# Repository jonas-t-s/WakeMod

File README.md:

# WakeMod: An Open-Source Wake-up Transceiver Module

WakeMod is an open-source, ultra-low-power wake-up transceiver module designed for the 868 MHz ISM band,
facilitating easy integration of Wake-up Radio (WuR) capabilities into existing and new IoT systems. It aims
to significantly reduce idle power consumption while ensuring low-latency event responsiveness, crucial for
battery-powered, long-term deployments.

An in-depth analysis of the hardware can be found here: [arXiv](https://arxiv.org/abs/2505.21529)

> <div align="justify"> Large-scale IoT applications, such as asset tracking and remote sensing, demand multi-year battery lifetimes to minimize maintenance and operational costs. Traditional wireless protocols often employ duty cycling, introducing a tradeoff between latency and idle consumption -- both unsuitable for event-driven and ultra-low power systems. A promising approach to address these issues is the integration of always-on Wake-up Receivers (WuRs). They provide asynchronous, ultra-low power communication to overcome these constraints. This paper presents WakeMod, an open-source wake-up transceiver module for the 868 MHz ISM band. Designed for easy integration and ultra-low power consumption, it leverages the -75 dBm sensitive FH101RF WuR. WakeMod achieves a low idle power consumption of 6.9 µW while maintaining responsiveness with a sensitivity of -72.6 dBm. Reception of a wake-up call is possible from up to 130 m of distance with a -2.1 dBi antenna, consuming 17.7 µJ with a latency below 54.3 ms. WakeMod's capabilities have further been demonstrated in an e-ink price tag application, achieving 7.17 µW idle consumption and enabling an estimated 8-year battery life with daily updates on a standard CR2032 coin cell. WakeMod offers a practical solution for energy-constrained, long-term IoT deployments, requiring low-latency, and on-demand communication.</div>

If you use *WakeMod* in an academic or industrial context, please cite the following publication:

```bibtex
@misc{schultess25_wakem,
  author         = {Lukas Schulthess and Silvano Cortesi and Michele Magno},
  title          = {Wakemod: a 6.9uw Wake-Up Radio Module With -72.6dbm Sensitivity for On-Demand Iot},
  year           = 2025,
  doi            = {10.48550/ARXIV.2505.21529},
  url            = {https://arxiv.org/abs/2505.21529},
  eprint         = {2505.21529},
  archiveprefix  = {arXiv},
  primaryclass   = {cs.NI},
  DATE_ADDED     = {Sun Jun 1 12:42:45 2025},
}
```

## Features

*   Combines Wake-up Radio (WuR) Receiver and OOK Transmitter functionality.
*   Ultra-low power operation:
    *   Module idle consumption: 6.9 µW
    *   WuR sensitivity: -72.6 dBm
*   Onboard low-power STMicroelectronics STM32U031 MCU for control and I2C communication.
*   Frauenhofer FH101RF Wake-up Radio receiver (868.35 MHz).
*   Maxim Integrated MAX41462 OOK transmitter (868.35 MHz).
*   Analog Devices ADG918 RF switch for single antenna operation.
*   Standard I2C interface for communication with a host system.
*   Compact RFM69x-compatible footprint (16mm x 16mm).
*   Deep sleep mode controlled by `SYS_SDN` pin.
*   Interrupt output (`SYS_IRQ`) to signal received Wake-up Calls to the host.
*   Supports 6-byte custom payload transmission and reception.

## Hardware

*   **Main Components:**
    *   MCU: STMicroelectronics STM32U031
    *   WuR Receiver: Fraunhofer IIS FH101RF
    *   OOK Transmitter: Analog Devices MAX41462
    *   RF Switch: Analog Devices ADG918
*   **Footprint:** RFM69HW compatible (16mm x 16mm)
*   **Operating Frequency:** 868.35 MHz

### Pinout

| Pin Name  | Type   | Description                                                                    |
| :-------- | :----- | :----------------------------------------------------------------------------- |
| `VDD`     | Power  | Power Supply Voltage                                                           |
| `GND`     | Ground | Ground Connection                                                              |
| `SDA`     | I/O    | I2C Data Line                                                                  |
| `SCL`     | Input  | I2C Clock Line                                                                 |
| `SYS_SDN` | Input  | System Shutdown / Module Enable. **Active Low.** High for deep sleep.          |
| `SYS_IRQ` | Output | Interrupt Request to Host. **Active High.** Signals a Wake-up event occurred.  |
| `ANT`     | RF     | Antenna connection                                                             |

**Note:** While the footprint matches RFM69, the interface is **I2C**, not SPI. All other pins are currently unused.

## Firmware

The firmware architecture of the WakeMod module is optimized for ultra-low power consumption, keeping the
STM32U031 MCU in shutdown mode as much as possible. Critical data is retained in backup registers during
shutdown.

The MCU wakes up based on three primary sources:
1.  **System Reset:** The MCU transitions immediately back to shutdown to minimize power consumption.
2.  **WuR IRQ:** Upon a wake-up triggered by the FH101RF (e.g., address match), the module clears the
interrupt, retrieves the interrupt source and up to 6 bytes of payload data from the WuR. This information is
stored in the MCU's backup registers. The host MCU's `SYS_IRQ` pin is then asserted, and the module returns to     shutdown.
3.  **SYS_SDN Pin:** If the `SYS_SDN` pin transitions to low, the MCU wakes up and prepares its I2C slave     interface to receive commands from the host. When `SYS_SDN` returns high, the module re-enters shutdown.

## WakeMod as a Module: Detailed Usage

### Power States

*   **Active Mode:** When `SYS_SDN` is held LOW. The module is operational and ready to accept I2C 
commands.
*   **Deep Sleep Mode:** When `SYS_SDN` is HIGH. The module enters its lowest power state (STM32U031 in 
shutdown, peripherals off). I2C communication is disabled. The FH101RF Wake-up Radio remains functional and 
listening. To wake the module for I2C communication, bring `SYS_SDN` LOW. Allow a short time for the module to     initialize before sending I2C commands.

### Interrupt Handling (`SYS_IRQ`)

*   The `SYS_IRQ` pin becomes active (HIGH) when the FH101RF detects a valid Wake-up condition (e.g., matching address, pattern received) and the internal STM32U031 has processed this event.
*   The host system should detect this interrupt (e.g., on a rising edge).
*   After detecting the interrupt, the host should query the module using the `IRQ Reason` command (0x03) via I2C to determine the cause and retrieve any associated data.
*   Reading the `IRQ Reason` register de-asserts the `SYS_IRQ` pin. Reading it multiple times will return the same last IRQ reason until a new WuR event occurs.

### Communication Protocol (I2C)

*   **Interface:** I2C Slave
*   **Slave Address:** `0x2E` (7-bit address)
*   **Speed:** Max 10 kHz
*   **Control:** I2C communication is only possible when the `SYS_SDN` pin is LOW.

#### I2C Commands Overview

The WakeMod module supports four main commands initiated by the host MCU:

1.  **`WhoAmI` (0x00):** Reads a static device identifier. Used to verify communication.
2.  **`SetupWuR` (0x01):** Configures the FH101RF Wake-up Radio. This includes setting the 16-bit wake-up address, data rates (low and fast), and IRQ source mask. This command triggers a full calibration of the FH101RF.
3.  **`SendWuC` (0x02):** Transmits a Wake-up Call (WuC) using the MAX41462 OOK transmitter. This includes the target 16-bit wake-up address, data rates, and an optional 6-byte data payload. The internal STM32U031 
uses SPI for accurate timing of the preamble and address/payload transmission to the MAX41462.
4.  **`IRQReason` (0x03):** Retrieves the reason for the last wake-up event (from the FH101RF) and any received payload data. This data is read from the STM32U031's backup registers.

#### I2C Transaction Structure

*   **Write Operations (Host to WakeMod):**
    *   Used for `SetupWuR` (0x01) and `SendWuC` (0x02).
    *   The host initiates an I2C WRITE transaction to the slave address (`0x2E`).
    *   The host sends a total of **12 bytes** in a single transaction:
        1.  The 1-byte Command (e.g., `0x01` for `SetupWuR`).
        2.  Followed by 11 data bytes (Bytes 0-10 as defined in the table below).
    *   Example (`SendWuC`):
        `START | (0x2E << 1) | W | ACK | <CMD_BYTE (0x02)> | ACK | <Data Byte 0> | ACK | ... | <Data Byte     10> | ACK | STOP`

*   **Read Operations (Host from WakeMod):**
    *   Used for `WhoAmI` (0x00) and `IRQ Reason` (0x03).
    *   A combined I2C write-then-read sequence is used:
        1.  **Write Address Phase:** Host initiates an I2C WRITE transaction to `0x2E`. Send only **1 
byte**: the Command Byte (e.g., `0x00` for `WhoAmI`).
        2.  **Read Data Phase:** Host initiates an I2C READ transaction to `0x2E`. Read exactly **8 
bytes** of data from the module (Bytes 0-7 as defined in the table below).
    *   Example (`WhoAmI`):
        *   `START | (0x2E << 1) | W | ACK | <CMD_BYTE (0x00)> | ACK | REP_START | (0x2E << 1) | R | ACK |     <Read Byte 0> | ACK | ... | <Read Byte 7> | NACK | STOP`

#### I2C Command Byte Layout

| Command / Register       | Value | Type  | Byte 0                     | Byte 1                     | Byte 2                | Byte 3                | Byte 4                    | Byte 5                      | Byte     6             | Byte 7             | Byte 8             | Byte 9             | Byte 10            |
| :----------------------- | :---- | :---- | :------------------------- | :------------------------- | :-------------------- | :-------------------- | :------------------------ | :-------------------------- | :----------------- | :----------------- | :----------------- | :----------------- | :----------------- |
| **WhoAmI**               | 0x00  | Read  | `0x42` (ID MSB)            | `0x42` (ID LSB)            | `0x00` (Padding)      | `0x00` (Padding)      | `0x00` (Padding)          | `0x00` (Padding)            | `0x00` (Padding)   | `0x00` (Padding)   | *N/A*              | *N/A*              | *N/A*              |
| **SetupWuR**             | 0x01  | Write | Wake-up Addr [15:8]        | Wake-up Addr [7:0]         | Low     Data Rate (enum)  | Fast Data Rate (enum) | IRQ Source Mask           | (Active Branches<<2)|IDM_CTRL             | Reserved `0x00`    | Reserved `0x00`    | Reserved `0x00`    | Reserved `0x00`    | Reserved `0x00`    |
| **SendWuC**              | 0x02  | Write | Wake-up Addr [15:8]        | Wake-up Addr [7:0]         | Low     Data Rate (enum)  | Fast Data Rate (enum) | Send Add. Data Flag (LSb)   | Add. Data [0]               | Add.     Data [1]      | Add. Data [2]      | Add. Data [3]      | Add. Data [4]      | Add. Data [5]      |
| **IRQ Reason**           | 0x03  | Read  | IRQ Source Flags           | Recv Add. Data Flag (LSb)  | Received Data [0]     | Received Data [1]     | Received Data [2]         | Received Data [3]           | Received Data [4]  | Received Data [5]  | *N/A*              | *N/A*              | *N/A*              |

**Table Key:**

*   **Value:** The byte sent by the host to select the command/register.
*   **Type:** Indicates if the operation is a Read from or Write to the module *from the host's 
perspective*.
*   **Bytes 0-10 (Write):** Data payload sent by the host *after* the Command Byte for write operations. 
Total 11 data bytes.
*   **Bytes 0-7 (Read):** Data payload returned by the module during the read phase of a read operation. 
Total 8 data bytes.
*   **Wake-up Addr [15:8]:** Most Significant Byte (MSB) of the 16-bit Wake-up Address.
*   **Wake-up Addr [7:0]:** Least Significant Byte (LSB) of the 16-bit Wake-up Address.
*   **Data Rate (enum):** See `phy_speed` Enum Values table below.
*   **IRQ Source Mask/Flags:** See IRQ Source Bits table below. Bitmask used in `SetupWuR` (Byte 4) to 
enable specific FH101RF interrupt sources, or flags indicating occurred interrupts in `IRQ Reason` (Byte 0).
*   **Send Add. Data Flag (LSb):** Least Significant Bit of Byte 4 for `SendWuC`. `1` = Additional Data in     Bytes 5-10 (Add. Data [0-5]) is valid and should be sent. `0` = Additional Data is ignored (but bytes 5-10 
must still be sent, typically as `0x00`).
*   **Recv Add. Data Flag (LSb):** Least Significant Bit of Byte 1 for `IRQ Reason`. `1` = Received Data 
in Bytes 2-7 (Received Data [0-5]) is valid. `0` = No valid received data (Bytes 2-7 may be undefined).
*   **Add. Data [0-5] / Received Data [0-5]:** The 6-byte additional data payload for transmission or 
reception.
*   **Reserved / Padding:** These bytes must be included in the I2C transaction but their value is 
typically ignored or should be `0x00`. They ensure the fixed transaction length.
*   ***N/A*:** Not applicable for that transaction type (Reads return 8 data bytes, Writes expect 11 data     bytes following the command byte).

#### Data Definitions

##### `phy_speed` Enum Values (as per `OLDREADME.md` I2C values)
These values are used in the `SetupWuR` and `SendWuC` commands for the Low/Fast Data Rate bytes.

| Value (for I2C) | Speed (bps) |
| :-------------- | :---------- |
| 0x02            | 1024        |
| 0x03            | 2048        |
| 0x04            | 4096        |
| 0x05            | 8192        |
| 0x06            | 16384       |
| 0x07            | 32768       |

*Note:* For OOK transmission via MAX41462, data rates below 1024 bps (e.g., 256, 512 bps) do not work due to the MAX41462's auto-shutdown functionality. The FH101RF itself supports these lower rates for reception.

##### IRQ Source Bits (Byte 4 in `SetupWuR` / Byte 0 in `IRQ Reason`)
This byte indicates the cause of the interrupt (`IRQ Reason`) or configures which FH101RF events can cause an interrupt (`SetupWuR`). Multiple bits can be set. These bits correspond to the FH101RF's interrupt 
sources.

| Bit | Description                  | Notes (Primarily for FH101RF internal events)             |
| :-- | :--------------------------- | :-------------------------------------------------------- |
| 7   | Cyclic Timer Alarm           | Cyclic timer target reached.                              |
| 6   | RTC Timer Alarm              | One of the 4 RTC timers reached its target.               |
| 5   | ID Match & LDR               | Valid ID received, followed by transition to LDR mode.    |
| 4   | ID Match & FIFO Filled       | Valid ID received, followed by FIFO being filled.         |
| 3   | Correlation Pattern Match    | OOK data matches selected correlation sequence.           |
| 2   | FIFO Buffer Filled           | FIFO filled to configured length (e.g. 6 bytes for payload).|
| 1   | FIFO Overflow                | More data received than FIFO capacity.                    |
| 0   | ID Match                     | Received Fast Data Packet matches configured 16-bit ID.   |

### Basic Usage Flow

1.  **Power On & Enable:** Ensure `VDD` and `GND` are connected. Pull `SYS_SDN` LOW to enable the module. Wait briefly for startup if it was in deep sleep.
2.  **(Optional) Verify Communication:** Perform a `WhoAmI` (0x00) read sequence. Check for `0x4242` in 
the first two bytes.
3.  **Configure Receiver:** Perform a `SetupWuR` (0x01) write sequence with:
    *   Your desired 16-bit `Wake-up Address`.
    *   The `Low Data Rate` and `Fast Data Rate` (see `phy_speed` enum).
    *   The `IRQ Source Mask` to enable interrupts for relevant events (e.g., bit 0 for ID Match, bit 4 
for ID Match & FIFO Filled if expecting payload).
4.  **Enter Low Power (Host):** The host can now enter its own low-power mode, monitoring the `SYS_IRQ` 
pin. The WakeMod is now listening. Make sure `SYS_SDN` is pulled high for WakeMod to enter low-power state.
5.  **Handle Interrupt from WakeMod:** When `SYS_IRQ` goes HIGH:
    *   The host wakes up.
    *   Perform an `IRQ Reason` (0x03) read sequence (possibly short delay needed before readout).
    *   Parse `Byte 0` (IRQ Source Flags) to understand why the interrupt occurred.
    *   Check `Byte 1` (Recv Add. Data Flag). If its LSB is `1`, the 6 bytes of `Received Data` (Bytes 
2-7) are valid. Process this data.
    *   The read operation of `IRQ Reason` clears the `SYS_IRQ` pin on the WakeMod.
6.  **(Optional) Transmit a Wake-up Call:** If the host needs to wake another device:
    *   Ensure `SYS_SDN` is LOW.
    *   Perform a `SendWuC` (0x02) write sequence with:
        *   The target device's 16-bit `Wake-up Address`.
        *   `Low Data Rate` and `Fast Data Rate`.
        *   `Send Add. Data Flag` (set LSB of Byte 4 to `1` if sending payload).
        *   The 6-byte `Add. Data` payload (Bytes 5-10) if applicable.
7.  **Enter Deep Sleep (WakeMod):** When I2C communication is not needed for extended periods, set 
`SYS_SDN` HIGH to put the WakeMod into its lowest power deep sleep mode. The WuR (FH101RF) remains active.

## Folder Structure

*   `fw/Core/Src`: Contains the main source files for the STM32U031 firmware, including `main.c`, `i2c_slave.c` (I2C command handling), `utils.c` (helper functions), and HAL drivers.
*   `fw/Core/Inc`: Contains the corresponding header files, including `main.h`, `utils.h` (definitions, enums).
*   Other folders (`Drivers`, `Middlewares`, etc.) contain STM32CubeMX generated files and libraries.

## License

See the `LICENSE` file of the firmware respective hardware for details.

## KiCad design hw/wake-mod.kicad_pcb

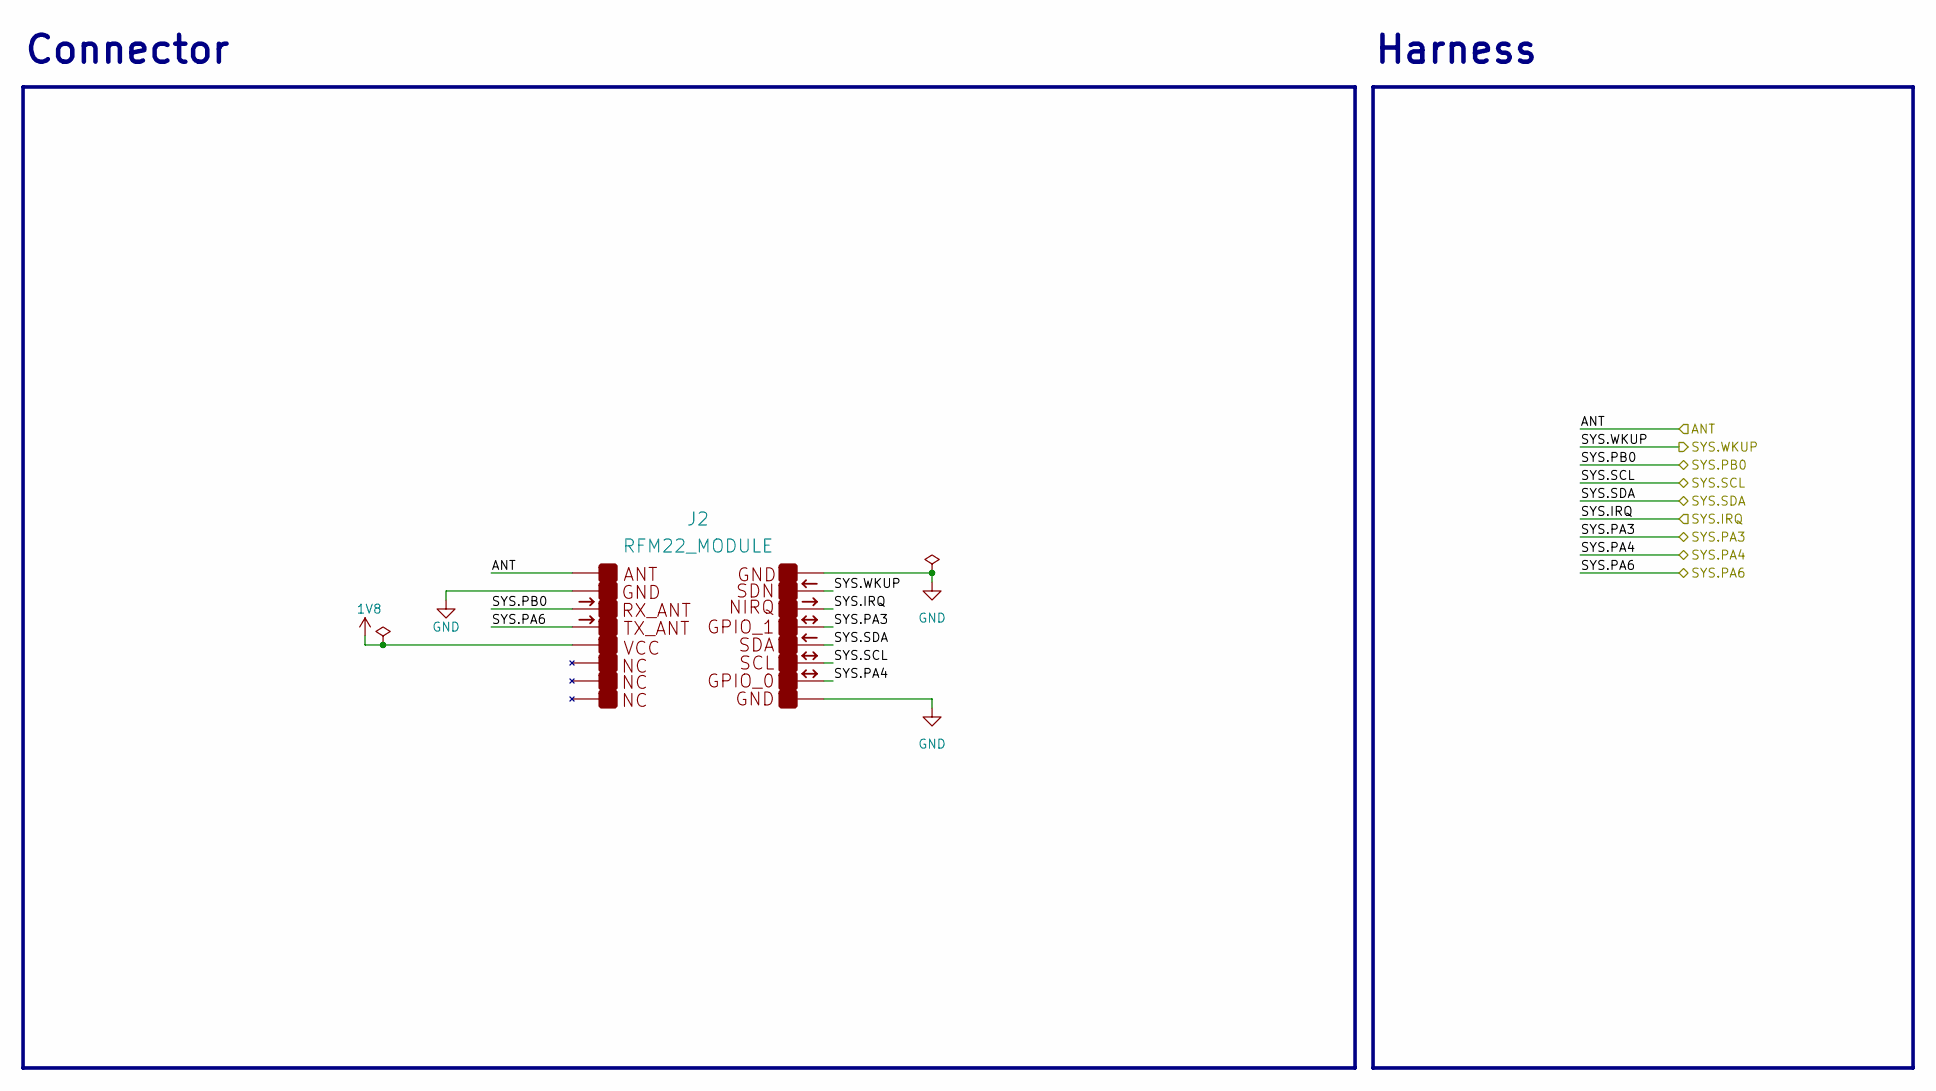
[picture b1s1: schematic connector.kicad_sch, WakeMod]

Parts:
J2: RFM22_MODULE; MPN RFM22_MODULE

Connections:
1V8: J2.5 (VCC); also elsewhere on the board
/connector/ANT: J2.1 (ANT); also elsewhere on the board
/connector/SYS.IRQ: J2.14 (NIRQ); also elsewhere on the board
/connector/SYS.PA3: J2.13 (GPIO_4); also elsewhere on the board
/connector/SYS.PA4: J2.10 (GPIO_3); also elsewhere on the board
/connector/SYS.PA6: J2.4 (TX_ANT); also elsewhere on the board
/connector/SYS.PB0: J2.3 (RX_ANT); also elsewhere on the board
/connector/SYS.SCL: J2.11 (SCL); also elsewhere on the board
/connector/SYS.SDA: J2.12 (SDA); also elsewhere on the board
/connector/SYS.WKUP: J2.15 (SDN); also elsewhere on the board
GND: J2.2 (GND), J2.9 (GND), J2.16 (GND); also elsewhere on the board

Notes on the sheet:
Harness
Connector

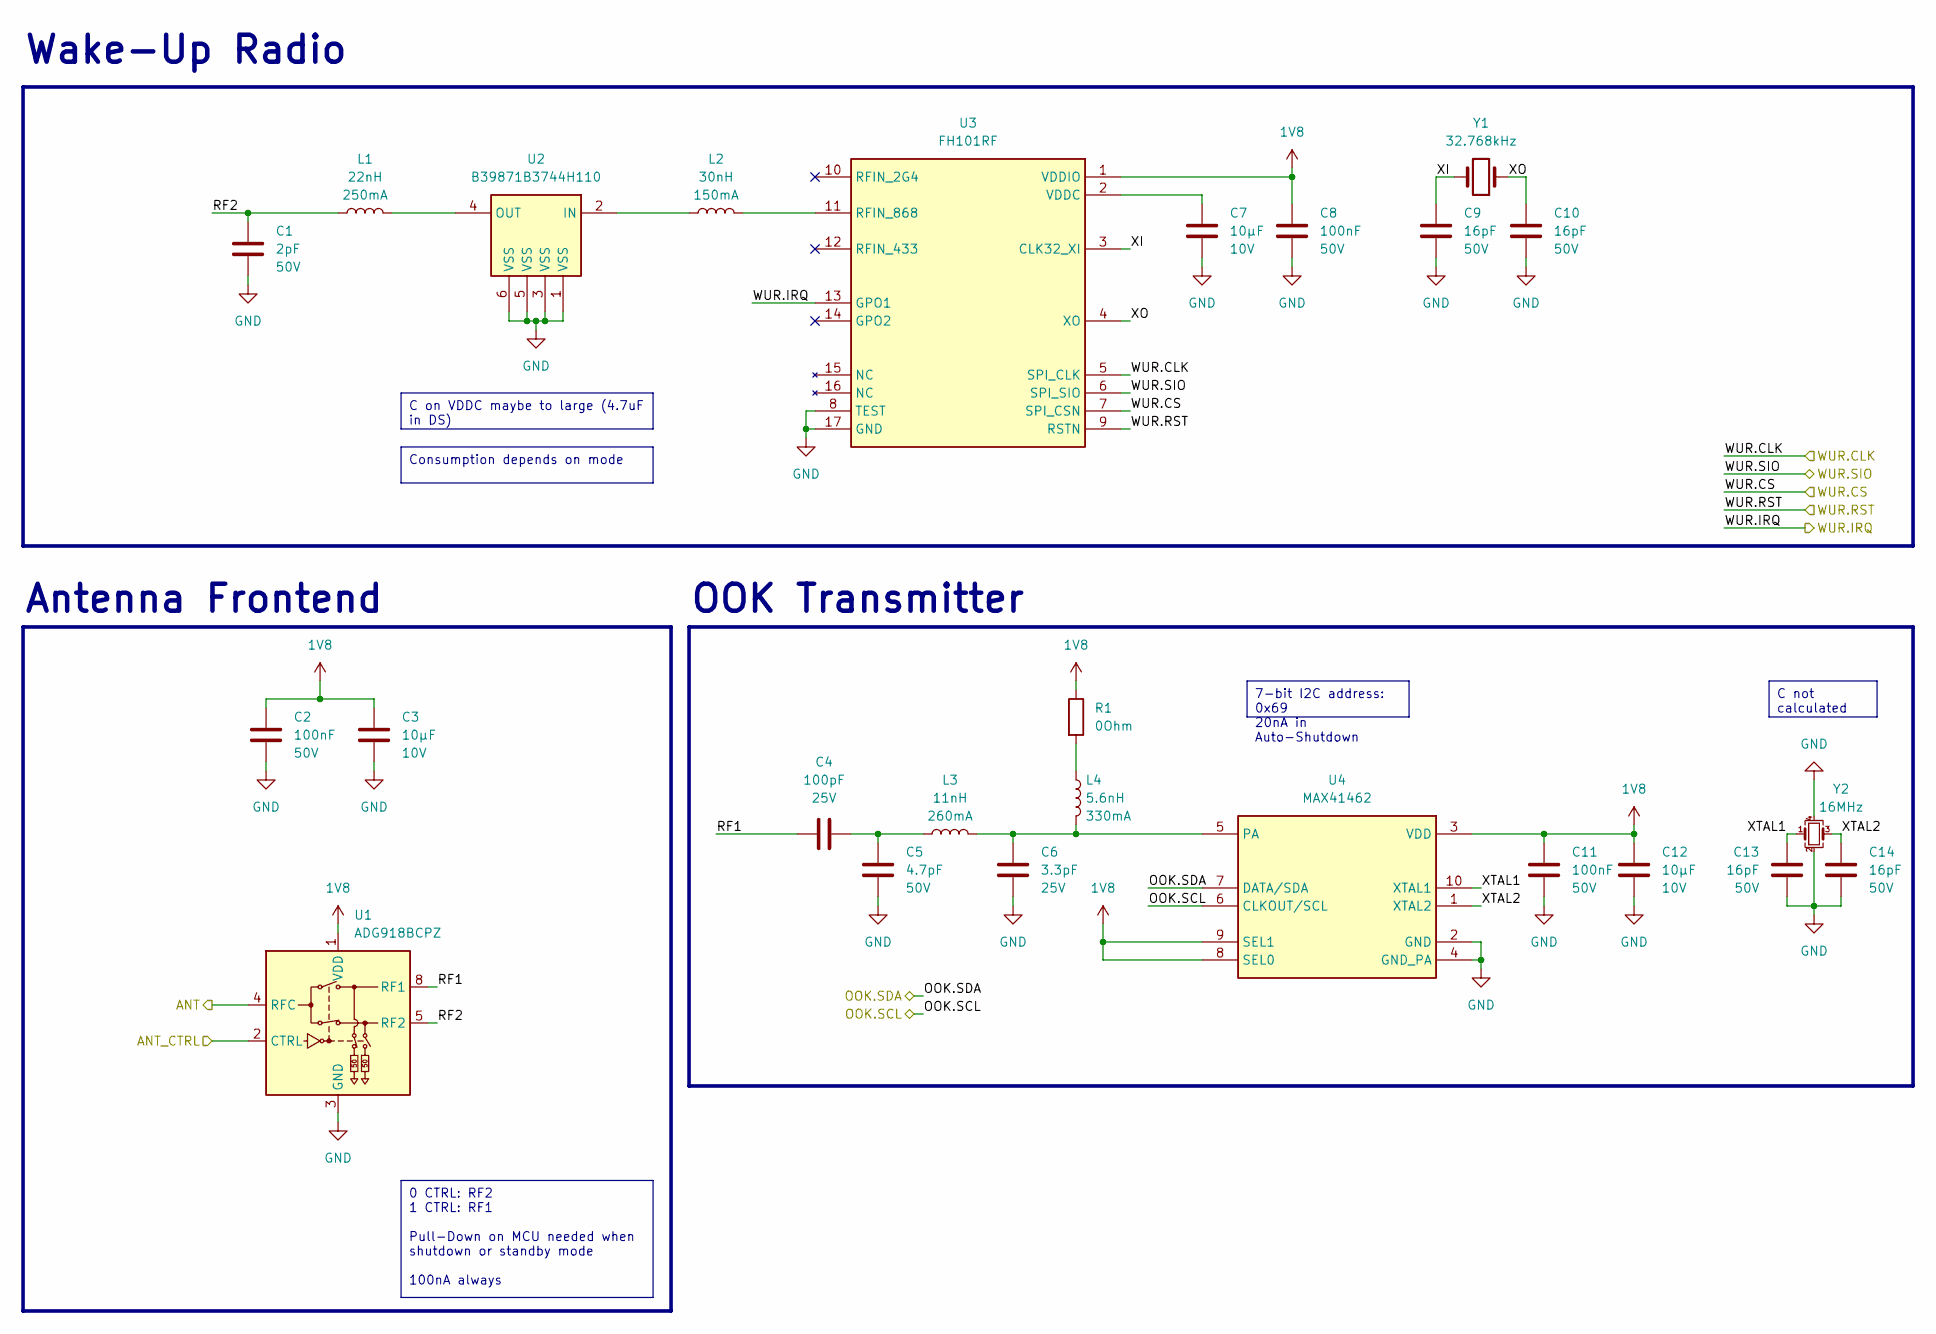
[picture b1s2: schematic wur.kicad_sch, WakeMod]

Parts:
C1: 2pF; C_0201_0603Metric; Voltage 50V; Tolerance 0.05pF; MPN GJM0335C1H2R0WB01D
C2, C8, C11: 100nF; C_0402_1005Metric; Voltage 50V; Tolerance 10%; MPN GRM155R71H104KE14J
C3, C7, C12: 10μF; C_0402_1005Metric; Voltage 10V; Tolerance 20%; MPN GRM155R61A106ME11D
C4: 100pF; C_0201_0603Metric; Voltage 25V; Tolerance 1%; MPN GRM0335C1E101FA01D
C5: 4.7pF; C_0201_0603Metric; Voltage 50V; Tolerance 0.05pF; MPN GJM0335C1H4R7WB01D
C6: 3.3pF; C_0201_0603Metric; Voltage 25V; Tolerance 0.05pF; MPN GJM0335C1E3R3WB01D
C9, C10, C13, C14: 16pF; C_0402_1005Metric; Voltage 50V; Tolerance 5%; MPN GRM1555C1H160JA01D
L1: 22nH; L_0201_0603Metric; Tolerance 3%; MPN LQP03HQ22NH02D
L2: 30nH; L_0201_0603Metric; Tolerance 3%; MPN LQP03HQ30NH02D
L3: 11nH; L_0201_0603Metric; Tolerance 5%; MPN LQW03AW11NJ00D
L4: 5.6nH; L_0201_0603Metric; Tolerance 5%; MPN LQW03AW5N6J00D
R1: 0Ohm; R_0201_0603Metric; Tolerance 1.00%; MPN ERJ-1GN0R00C
U1: ADG918BCPZ; LFCSP-8-1EP_3x3mm_P0.5mm_EP1.45x1.74mm; MPN ADG918BCPZ
U2: B39871B3744H110; QUALCOMM_B3744; MPN B39871B3744H110
U3: FH101RF; RFICIENT_QFN-16; MPN FH101RF
U4: MAX41462; MAXIM_MINI-SO-10; MPN MAX41462
Y1: 32.768kHz; ECS_ECX-12R; MPN ECS-.327-12.5-12R
Y2: 16MHz; Oscillator_SMD_SeikoEpson_SG210-4Pin_2.5x2.0mm; MPN ECS-160-8-36-CKM

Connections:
1V8: C2.2, C3.1, C8.1, C11.1, C12.1, R1.1, U1.1 (VDD), U3.1 (VDDIO), U4.3 (VDD), U4.8 (SEL0), U4.9 (SEL1); also elsewhere on the board
/connector/ANT: U1.4 (RFC); also elsewhere on the board
/mcu/ANT_CTRL: U1.2 (CTRL); also elsewhere on the board
/mcu/OOK.SCL: U4.6 (CLKOUT/SCL); also elsewhere on the board
/mcu/OOK.SDA: U4.7 (DATA/SDA); also elsewhere on the board
/mcu/WUR.CLK: U3.5 (SPI_CLK); also elsewhere on the board
/mcu/WUR.CS: U3.7 (SPI_CSN); also elsewhere on the board
/mcu/WUR.IRQ: U3.13 (GPO1); also elsewhere on the board
/mcu/WUR.RST: U3.9 (RSTN); also elsewhere on the board
/mcu/WUR.SIO: U3.6 (SPI_SIO); also elsewhere on the board
/wur/RF1: C4.1, U1.8 (RF1)
/wur/RF2: C1.1, L1.1, U1.5 (RF2)
/wur/XI: C9.1, U3.3 (CLK32_XI), Y1.1
/wur/XO: C10.1, U3.4 (XO), Y1.2
/wur/XTAL1: C13.1, U4.10 (XTAL1), Y2.1
/wur/XTAL2: C14.1, U4.1 (XTAL2), Y2.3
GND: C1.2, C2.1, C3.2, C5.2, C6.2, C7.2, C8.2, C9.2, C10.2, C11.2, C12.2, C13.2, C14.2, U1.3 (GND), U1.6 (GND), U1.7 (GND), U1.9 (GND), U2.1 (VSS), U2.3 (VSS), U2.5 (VSS), U2.6 (VSS), U3.8 (TEST), U3.17 (GND), U4.2 (GND), U4.4 (GND_PA), Y2.2, Y2.4; also elsewhere on the board
unnamed: C4.2, C5.1, L3.1
unnamed: L4.1, R1.2
unnamed: L2.1, U2.2 (IN)
unnamed: L1.2, U2.4 (OUT)
unnamed: L2.2, U3.11 (RFIN_868)
unnamed: C7.1, U3.2 (VDDC)
unnamed: C6.1, L3.2, L4.2, U4.5 (PA)

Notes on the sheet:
Wake-Up Radio
OOK Transmitter
Antenna Frontend
C on VDDC maybe to large (4.7uF in DS)
Consumption depends on mode
7-bit I2C address: 0x69 20nA in Auto-Shutdown
0 CTRL: RF2 1 CTRL: RF1 Pull-Down on MCU needed when shutdown or standby mode 100nA always
C not calculated

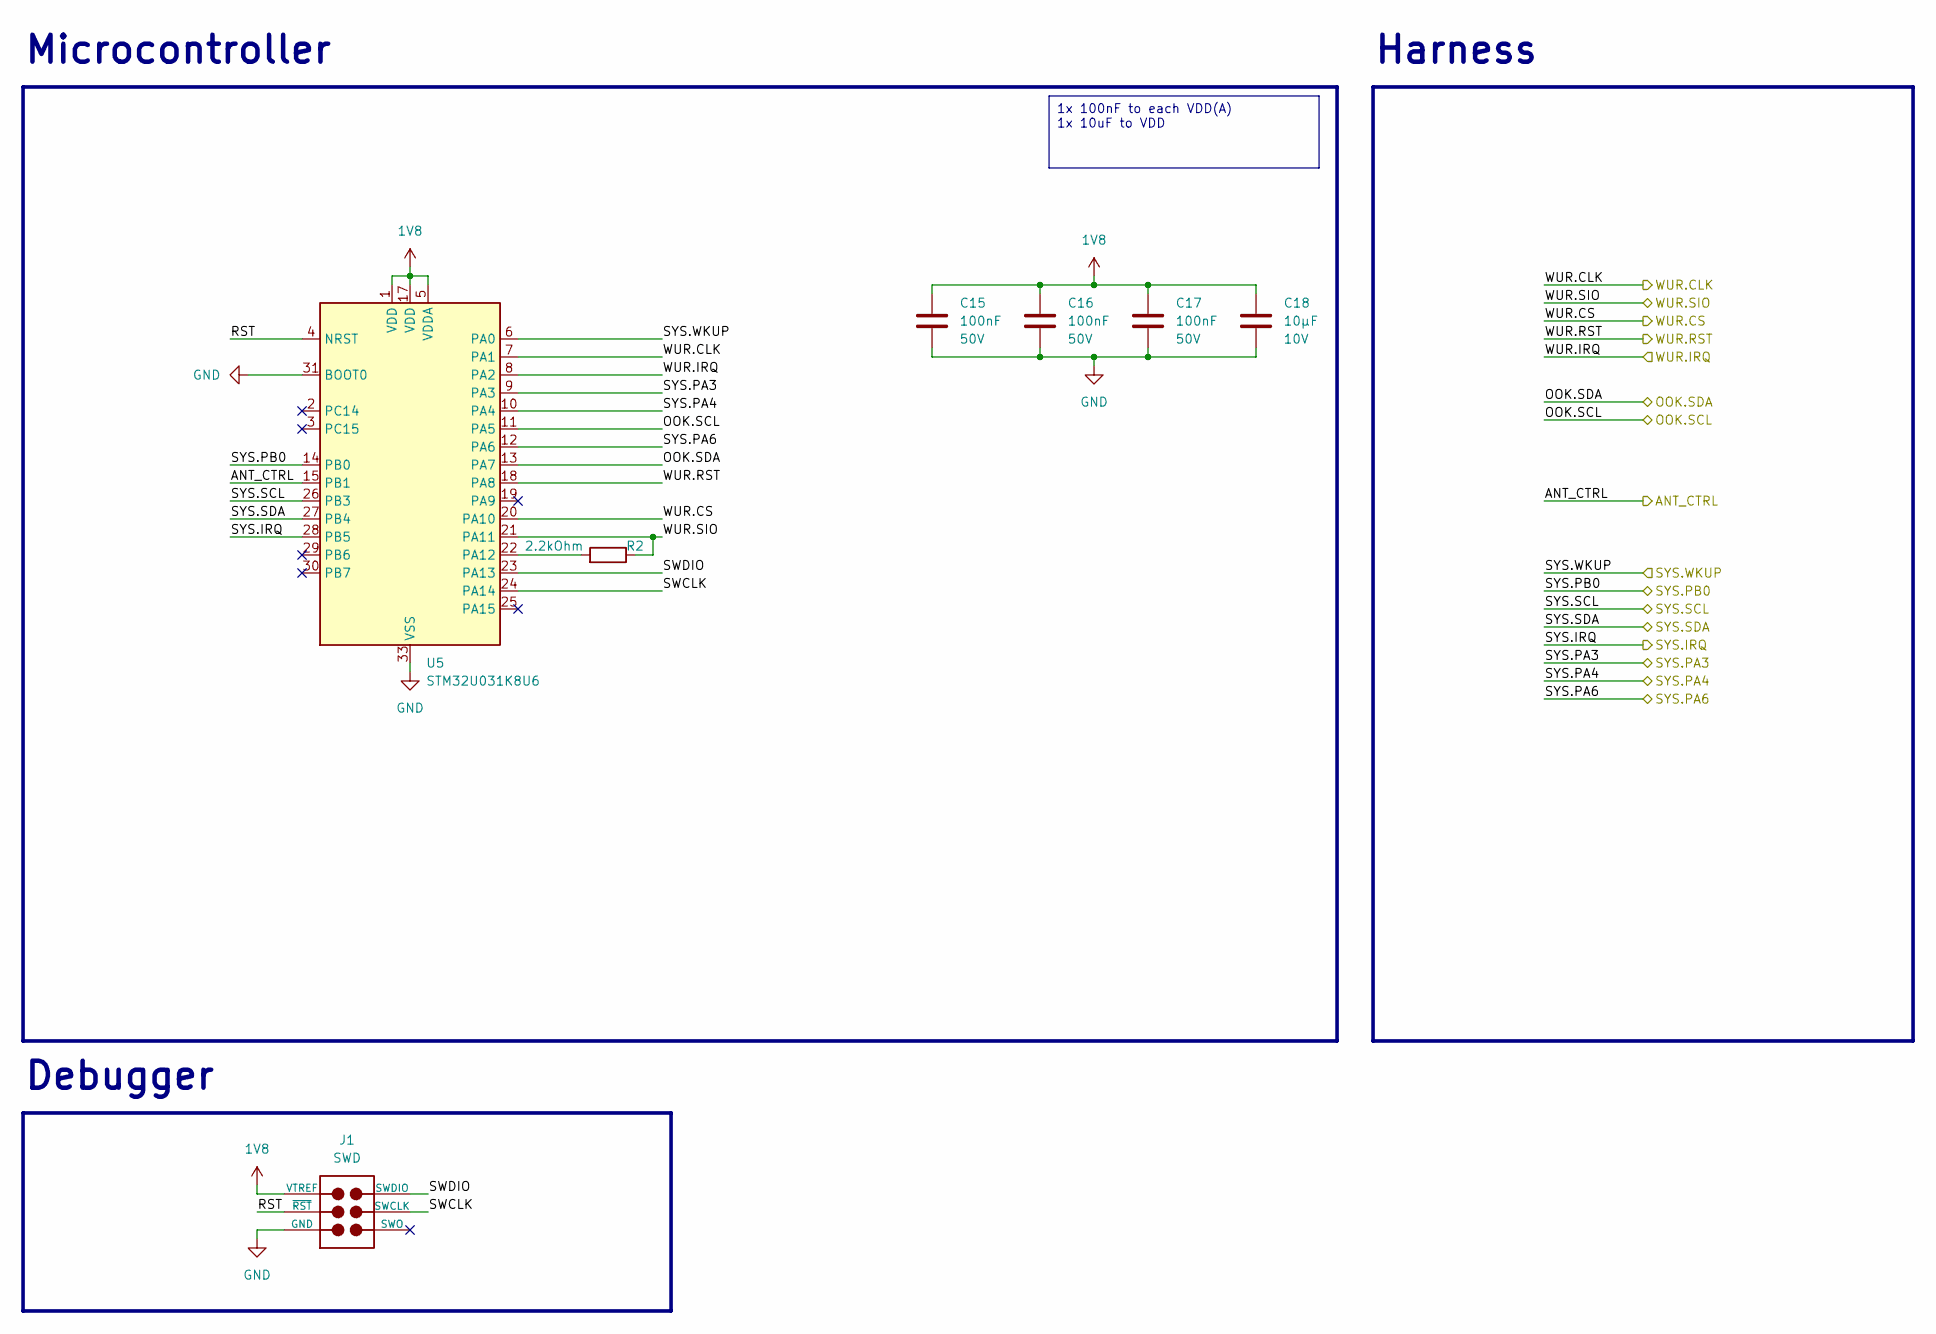
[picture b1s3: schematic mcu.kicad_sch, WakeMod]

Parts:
C15, C16, C17: 100nF; C_0402_1005Metric; Voltage 50V; Tolerance 10%; MPN GRM155R71H104KE14J
C18: 10μF; C_0402_1005Metric; Voltage 10V; Tolerance 20%; MPN GRM155R61A106ME11D
J1: SWD; TAGCONNECT_TC2030-MCP-NL
R2: 2.2kOhm; R_0402_1005Metric; Tolerance 1.00%; MPN ERJ-2RKF2201X
U5: STM32U031K8U6; QFN-32-1EP_5x5mm_P0.5mm_EP3.45x3.45mm; MPN STM32U031K8U6

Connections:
1V8: C15.1, C16.1, C17.1, C18.1, J1.1 (VTREF), U5.1 (VDD), U5.5 (VDDA), U5.17 (VDD); also elsewhere on the board
/connector/SYS.IRQ: U5.28 (PB5); also elsewhere on the board
/connector/SYS.PA3: U5.9 (PA3); also elsewhere on the board
/connector/SYS.PA4: U5.10 (PA4); also elsewhere on the board
/connector/SYS.PA6: U5.12 (PA6); also elsewhere on the board
/connector/SYS.PB0: U5.14 (PB0); also elsewhere on the board
/connector/SYS.SCL: U5.26 (PB3); also elsewhere on the board
/connector/SYS.SDA: U5.27 (PB4); also elsewhere on the board
/connector/SYS.WKUP: U5.6 (PA0); also elsewhere on the board
/mcu/ANT_CTRL: U5.15 (PB1); also elsewhere on the board
/mcu/OOK.SCL: U5.11 (PA5); also elsewhere on the board
/mcu/OOK.SDA: U5.13 (PA7); also elsewhere on the board
/mcu/RST: J1.3 (~RST), U5.4 (NRST)
/mcu/SWCLK: J1.4 (SWCLK), U5.24 (PA14)
/mcu/SWDIO: J1.2 (SWDIO), U5.23 (PA13)
/mcu/WUR.CLK: U5.7 (PA1); also elsewhere on the board
/mcu/WUR.CS: U5.20 (PA10); also elsewhere on the board
/mcu/WUR.IRQ: U5.8 (PA2); also elsewhere on the board
/mcu/WUR.RST: U5.18 (PA8); also elsewhere on the board
/mcu/WUR.SIO: R2.1, U5.21 (PA11); also elsewhere on the board
GND: C15.2, C16.2, C17.2, C18.2, J1.5 (GND), U5.16 (VSS), U5.31 (BOOT0), U5.32 (VSS), U5.33 (VSS); also elsewhere on the board
unnamed: R2.2, U5.22 (PA12)

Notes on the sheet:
Debugger
Harness
Microcontroller
1x 100nF to each VDD(A) 1x 10uF to VDD

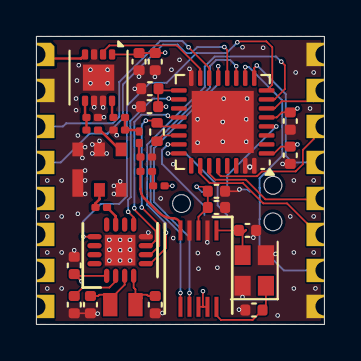
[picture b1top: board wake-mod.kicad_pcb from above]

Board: 4 copper layers, 16.0 x 16.0 mm, 33 parts (1 on the bottom side), 36 nets.

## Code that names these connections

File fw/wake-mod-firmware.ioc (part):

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Mcu.Name=STM32U031K8Ux
Mcu.Package=UFQFPN32
Mcu.UserName=STM32U031K8Ux
PA0-CK_IN.GPIOParameters=GPIO_Label
PA0-CK_IN.GPIO_Label=SYS_SDN
PA0-CK_IN.Signal=GPXTI0
PA1.GPIOParameters=GPIO_Label
PA1.GPIO_Label=WUR_CLK
PA1.Mode=Full_Duplex_Master
PA1.Signal=SPI2_SCK
PA10.GPIOParameters=PinState,GPIO_PuPd,GPIO_Label
PA10.GPIO_Label=WUR_CS
PA10.GPIO_PuPd=GPIO_PULLUP
PA10.PinState=GPIO_PIN_SET
PA10.Signal=GPIO_Output
PA11\ [PA9].GPIOParameters=GPIO_Label
PA11\ [PA9].GPIO_Label=WUR_MISO
PA11\ [PA9].Mode=Full_Duplex_Master
PA11\ [PA9].Signal=SPI2_MISO
PA12\ [PA10].GPIOParameters=GPIO_Label
PA12\ [PA10].GPIO_Label=WUR_MOSI
PA12\ [PA10].Mode=Full_Duplex_Master
PA12\ [PA10].Signal=SPI2_MOSI
PA13\ (SWDIO).GPIOParameters=GPIO_Label
PA13\ (SWDIO).GPIO_Label=SWDIO
PA13\ (SWDIO).Mode=Serial_Wire
PA13\ (SWDIO).Signal=DEBUG_JTMS-SWDIO
PA14\ (SWCLK).GPIOParameters=GPIO_Label
PA14\ (SWCLK).GPIO_Label=SWCLK
PA14\ (SWCLK).Mode=Serial_Wire
PA14\ (SWCLK).Signal=DEBUG_JTCK-SWCLK
PA2.GPIOParameters=GPIO_Label
PA2.GPIO_Label=WUR_IRQ
PA2.Mode=WakeUp4
PA2.Signal=PWR_WKUP4
PA5.GPIOParameters=GPIO_Label
PA5.GPIO_Label=DISABLE_IN_SW
PA5.Mode=TX_Only_Simplex_Unidirect_Master
PA5.Signal=SPI1_SCK
PA7.GPIOParameters=GPIO_Label
PA7.GPIO_Label=OOK_SDA
PA7.Mode=TX_Only_Simplex_Unidirect_Master
PA7.Signal=SPI1_MOSI
PA8.GPIOParameters=PinState,GPIO_PuPd,GPIO_Label
PA8.GPIO_Label=WUR_RST
PA8.GPIO_PuPd=GPIO_PULLUP
PA8.PinState=GPIO_PIN_SET
PA8.Signal=GPIO_Output
PB1.GPIOParameters=PinState,GPIO_PuPd,GPIO_Label
PB1.GPIO_Label=ANT_CTRL
PB1.GPIO_PuPd=GPIO_PULLDOWN
PB1.PinState=GPIO_PIN_RESET
PB1.Signal=GPIO_Output
PB3.GPIOParameters=GPIO_Label
PB3.GPIO_Label=SYS_SCL
PB3.Mode=I2C
PB3.Signal=I2C3_SCL
PB4.GPIOParameters=GPIO_Label
PB4.GPIO_Label=SYS_SDA
PB4.Mode=I2C
PB4.Signal=I2C3_SDA
PB5.GPIOParameters=GPIO_PuPd,GPIO_Label
PB5.GPIO_Label=SYS_IRQ
PB5.GPIO_PuPd=GPIO_PULLDOWN
PB5.Signal=GPIO_Output
RCC.HSE_VALUE=4000000
RCC.SYSCLKFreq_VALUE=16888888.888888888
RCC.SYSCLKSource=RCC_SYSCLKSOURCE_PLLCLK
board=custom

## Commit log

2025-05-13 [ADD] Hardware v1.1, Firmware
2025-06-01 Add citation informations
2025-07-04 [ADD] WakeMod image
2025-07-25 Change FH101RF_IDM_CTRL to the default value of the FH101RF.
2025-07-25 Document `(Active Branches << 2) | IDM_CTRL` usage in README.
2025-07-25 Added IDM_CTRL and active korrelbranches to I2C. Bits left: 3)

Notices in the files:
README.md:
License:
See the `LICENSE` file of the firmware respective hardware for details.
